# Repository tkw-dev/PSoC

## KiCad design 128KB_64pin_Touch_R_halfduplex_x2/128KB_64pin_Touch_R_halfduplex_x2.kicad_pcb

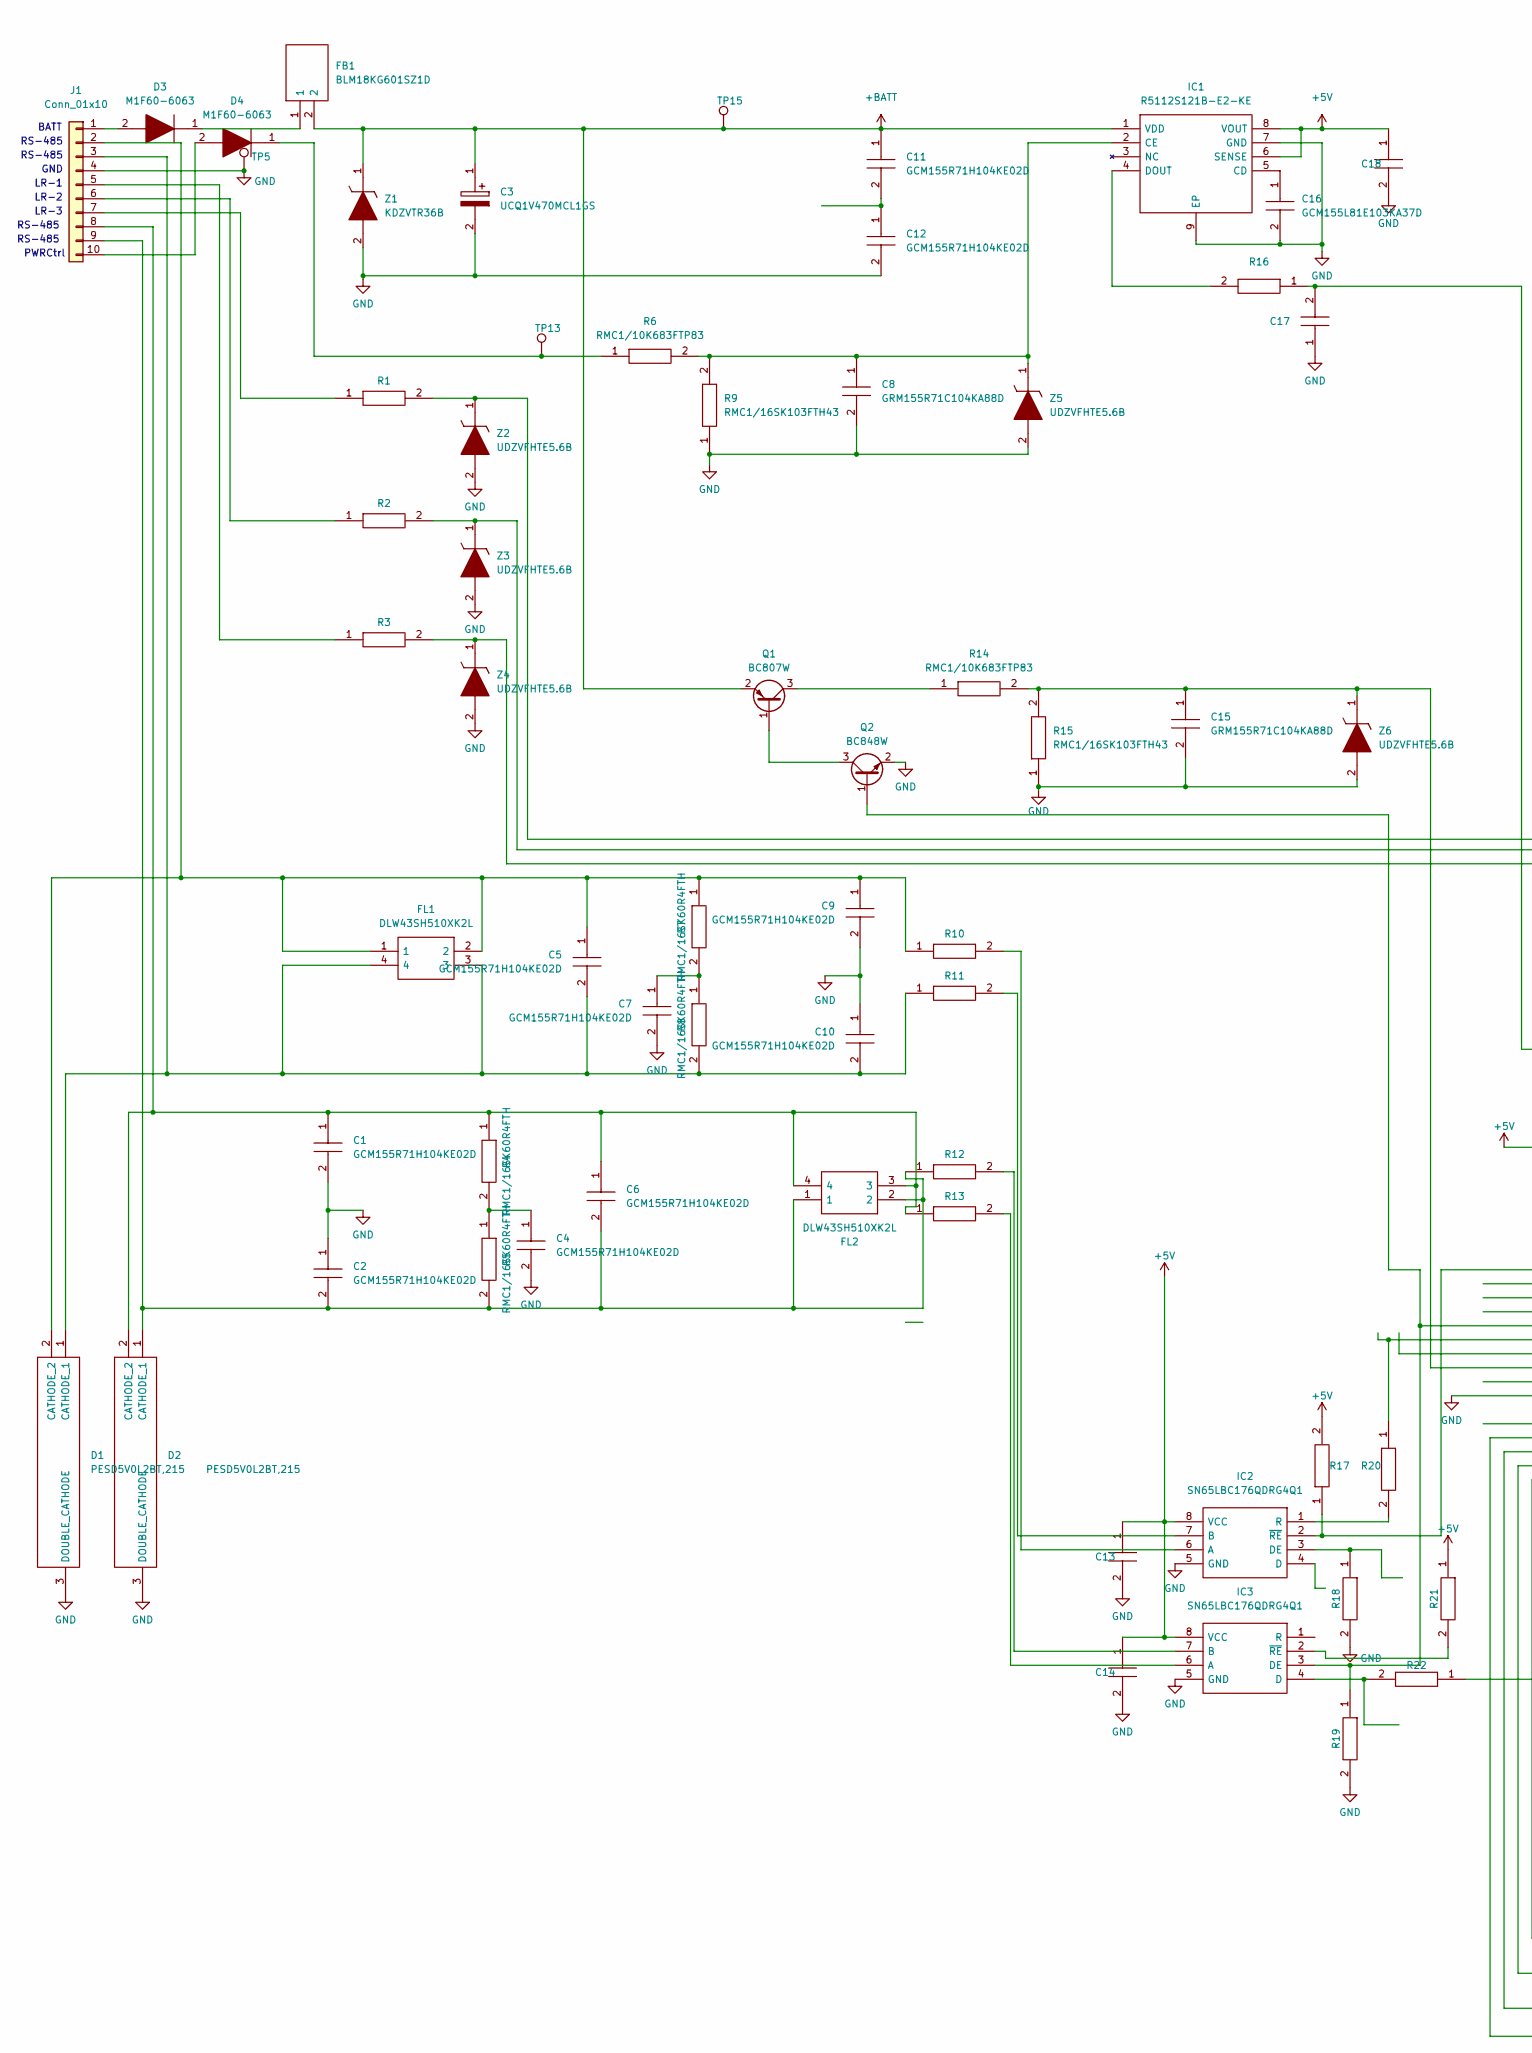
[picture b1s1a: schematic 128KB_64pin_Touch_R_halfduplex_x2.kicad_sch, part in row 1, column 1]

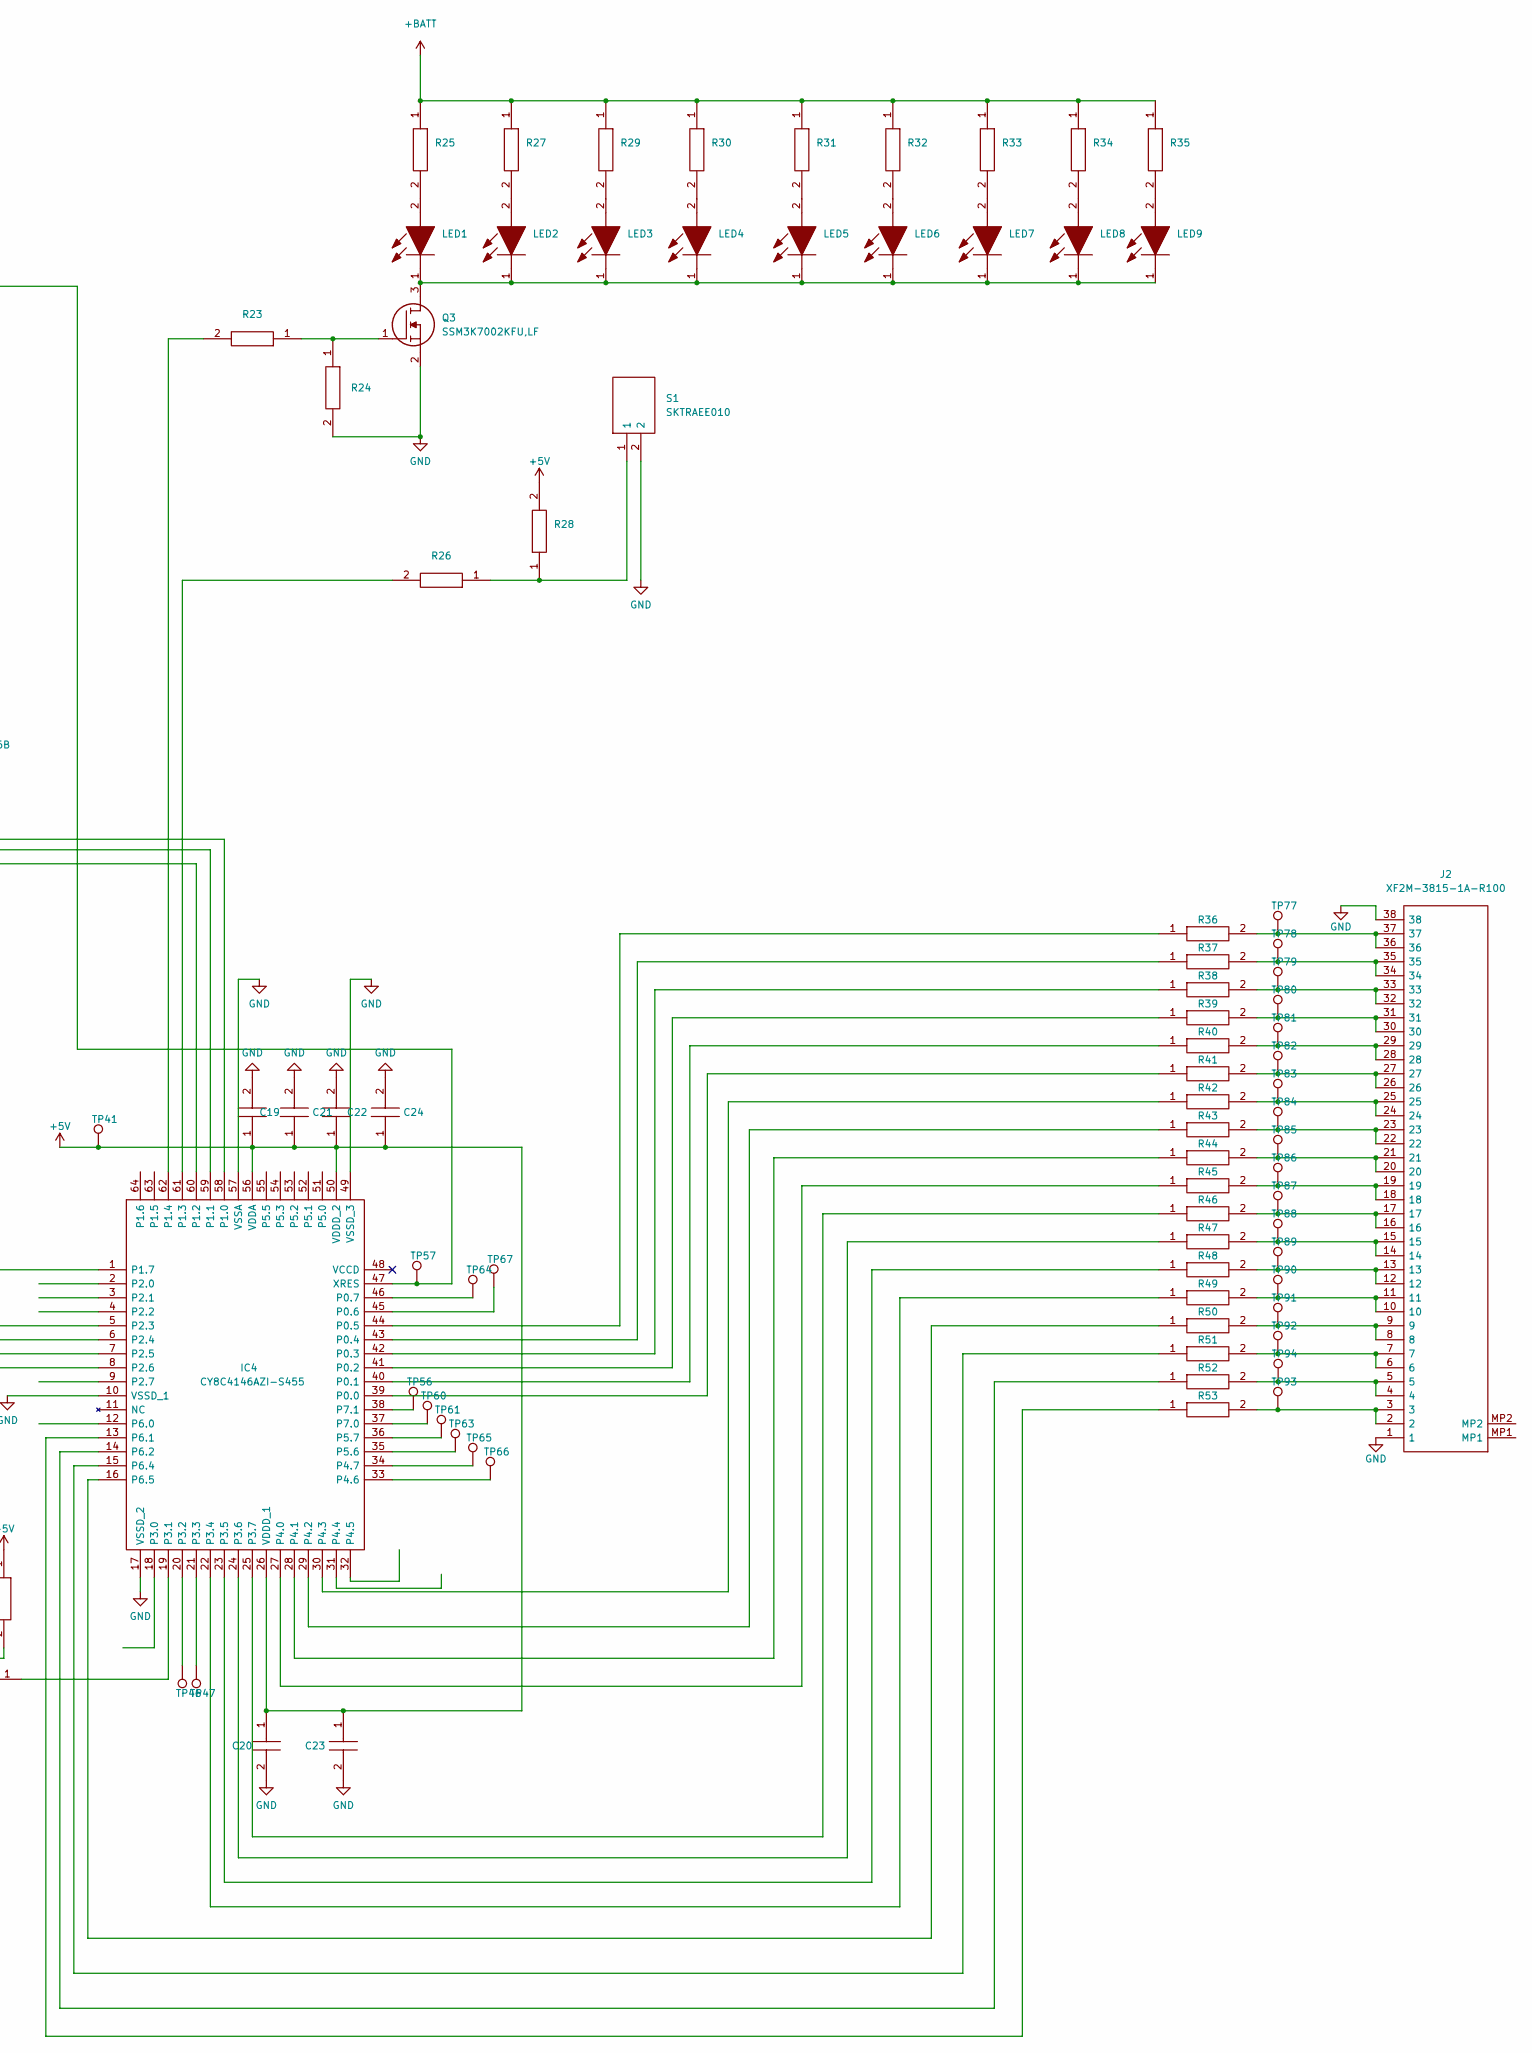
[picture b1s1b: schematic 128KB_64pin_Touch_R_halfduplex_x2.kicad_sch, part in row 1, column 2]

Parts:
C1, C2, C4, C5, C6, C7, C9, C10, C11, C12, C13, C14, C18, C19, C20, C22: GCM155R71H104KE02D; CAPC1005X55N; Mouser Part Number 81-GCM155R71H104KE2D
C3: UCQ1V470MCL1GS; CAPAE660X780N; Mouser Part Number 647-UCQ1V470MCL1GS
C8, C15: GRM155R71C104KA88D; CAPC1005X55N; Mouser Part Number N/A
C16: GCM155L81E103KA37D; CAPC1005X55N; Mouser Part Number 81-GCM155L81E103KA7D
C17: CL10B104JB8NNNC; CAPC1608X90N; Mouser Part Number 187-CL10B104JB8NNNC
C21, C23, C24: CGA3E2X5R1A105M080AA; CAPC1608X90N; Mouser Part Number 810-CGA3E2X5R1A105MA
D1, D2: PESD5V0L2BT,215; SOT95P230X110-3N; Manufacturer_Part_Number PESD5V0L2BT,215; Mouser Part Number 771-PESD5V0L2BT-T/R
D3, D4: M1F60-6063; SODFL3918X140N; Mouser Part Number 627-M1F60-6063
FB1: BLM18KG601SZ1D; BLM18EG121SH1D; Mouser Part Number 81-BLM18KG601SZ1D
FL1, FL2: DLW43SH510XK2L; DLW43SH110XK2K; Mouser Part Number 81-DLW43SH510XK2L
IC1: R5112S121B-E2-KE; SOIC127P620X160-9N; Manufacturer_Part_Number R5112S121B-E2-KE
IC2, IC3: SN65LBC176QDRG4Q1; SOIC127P600X175-8N; Mouser Part Number 595-N65LBC176QDRG4Q1
IC4: CY8C4146AZI-S455; QFP50P1200X1200X160-64N; Manufacturer_Part_Number CY8C4146AZI-S455; Mouser Part Number 727-CY8C4146AZI-S455
J1: Conn_01x10; JST_XH_B10B-XH-A_1x10_P2.50mm_Vertical
J2: XF2M-3815-1A-R100; XF2M38151AR100; Manufacturer_Part_Number XF2M-3815-1A-R100; Mouser Part Number 653-XF2M38151AR100
LED1, LED2, LED3, LED4, LED5, LED6, LED7, LED8, LED9: VLMR233T2V2-GS08; LEDM2214X140N; Mouser Part Number 78-VLMR233T2V2-GS08
Q1: BC807W; SOT-323_SC-70
Q2: BC848W; SOT-323_SC-70
Q3: SSM3K7002KFU,LF; SSM3K7002CFULF; Mouser Part Number 757-SSM3K7002KFULF
R1, R2, R3, R6, R14: RMC1/10K683FTP83; RESC2012X65N; Mouser Part Number 791-RMC1/10-103JTP
R4, R5, R7, R8: RMC1/16SK60R4FTH; RESC1608X55N; Manufacturer_Part_Number RMC16K270FTP
R9, R15, R23, R24, R26, R28: RMC1/16SK103FTH43; RESC1608X55N; Manufacturer_Part_Number RMC16K102FTP
R10, R11, R12, R13, R17, R18, R19, R20, R21, R22: RMC16K270FTP; RESC1608X55N; Manufacturer_Part_Number RMC16K270FTP
R16: RMC16K102FTP; RESC1608X55N; Manufacturer_Part_Number RMC16K102FTP
R25, R27, R29, R30, R31, R32, R33, R34, R35: ERJ-6ENF1502V; ERJ6ENF1000V; Mouser Part Number 667-ERJ-6ENF1502V
R36, R37, R38, R39, R40, R41, R42, R43, R44, R45, R46, R47, R48, R49, R50, R51, R52, R53: ERJ-2GEJ561X; RESC1005X40N; Mouser Part Number 667-ERJ-2GEJ561X
S1: SKTRAEE010; Mouser Part Number 688-SKTRAEE010
TP5, TP13, TP15, TP41, TP57, TP67: TestPoint; TestPoint_Pad_D2.5mm
TP46, TP47, TP56, TP60, TP61, TP63, TP64, TP65, TP66: TestPoint; TestPoint_Pad_D1.0mm
TP77, TP78, TP79, TP80, TP81, TP82, TP83, TP84, TP85, TP86, TP87, TP88, TP89, TP90, TP91, TP92, TP93, TP94: TestPoint; TestPoint_Pad_D0.5mm
Z1: KDZVTR36B; Mouser Part Number 755-KDZVTR36B
Z2, Z3, Z4, Z5, Z6: UDZVFHTE5.6B; SODFL2512X90N; Mouser Part Number 755-UDZVFHTE-175.6B

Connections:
+5V: C13.1, C14.1, C18.1, C19.1, C20.1, C21.1, C22.1, C23.1, C24.1, IC1.6 (SENSE), IC1.8 (VOUT), IC2.8 (VCC), IC3.8 (VCC), IC4.26 (VDDD_1), IC4.50 (VDDD_2), IC4.56 (VDDA), R17.2, R21.1, R28.2, TP41.1
+BATT: C3.1, C11.1, FB1.2, IC1.1 (VDD), Q1.2 (E), R25.1, R27.1, R29.1, R30.1, R31.1, R32.1, R33.1, R34.1, R35.1, TP15.1, Z1.1
GND: C1.2, C2.1, C3.2, C4.2, C7.2, C8.2, C9.2, C10.1, C12.2, C13.2, C14.2, C15.2, C16.2, C17.1, C18.2, C19.2, C20.2, C21.2, C22.2, C23.2, C24.2, D1.3 (DOUBLE_CATHODE), D2.3 (DOUBLE_CATHODE), IC1.7 (GND), IC1.9 (EP), IC2.5 (GND), IC3.5 (GND), IC4.10 (VSSD_1), IC4.17 (VSSD_2), IC4.49 (VSSD_3), IC4.57 (VSSA), J1.4, J2.1, J2.38, Q2.2 (E), Q3.2, R9.1, R15.1, R18.2, R19.2, R24.2, S1.2, TP5.1, Z1.2, Z2.2, Z3.2, Z4.2, Z5.2, Z6.2
unnamed: C1.1, C6.1, D2.2 (CATHODE_2), FL2.3, FL2.4, J1.8, R4.1, R13.1
unnamed: C4.1, R4.2, R5.1
unnamed: C5.1, C9.1, D1.2 (CATHODE_2), FL1.1, FL1.2, J1.2, R7.1, R10.1
unnamed: C7.1, R7.2, R8.1
unnamed: C5.2, C10.2, D1.1 (CATHODE_1), FL1.3, FL1.4, J1.3, R8.2, R11.1
unnamed: C11.2, C12.1
unnamed: C15.1, IC4.8 (P2.6), R14.2, R15.2, Z6.1
unnamed: C16.1, IC1.5 (CD)
unnamed: C17.2, IC4.47 (XRES), R16.1, TP57.1
unnamed: D3.1, FB1.1
unnamed: D3.2, J1.1
unnamed: D4.1, R6.1, TP13.1
unnamed: C2.2, C6.2, D2.1 (CATHODE_1), FL2.1, FL2.2, J1.9, R5.2, R12.1
unnamed: C8.1, IC1.2 (CE), R6.2, R9.2, Z5.1
unnamed: IC1.4 (DOUT), R16.2
unnamed: IC2.1 (R), R20.2
unnamed: IC2.2 (~RE), IC4.1 (P1.7), R17.1
unnamed: IC2.3 (DE), R18.1
unnamed: IC2.6 (A), R10.2
unnamed: IC2.7 (B), R11.2
unnamed: IC3.2 (~RE), R21.2
unnamed: IC3.3 (DE), IC4.5 (P2.3), Q2.1 (B), R19.1
unnamed: IC3.4 (D), R22.2
unnamed: IC3.6 (A), R13.2
unnamed: IC3.7 (B), R12.2
unnamed: IC4.6 (P2.4), R20.1
unnamed: IC4.13 (P6.1), R53.1
unnamed: IC4.14 (P6.2), R52.1
unnamed: IC4.15 (P6.4), R51.1
unnamed: IC4.16 (P6.5), R50.1
unnamed: IC4.19 (P3.1), R22.1
unnamed: IC4.20 (P3.2), TP46.1
unnamed: IC4.21 (P3.3), TP47.1
unnamed: IC4.22 (P3.4), R49.1
unnamed: IC4.23 (P3.5), R48.1
unnamed: IC4.24 (P3.6), R47.1
unnamed: IC4.25 (P3.7), R46.1
unnamed: IC4.27 (P4.0), R45.1
unnamed: IC4.28 (P4.1), R44.1
unnamed: IC4.29 (P4.2), R43.1
unnamed: IC4.30 (P4.3), R42.1
unnamed: IC4.33 (P4.6), TP66.1
unnamed: IC4.34 (P4.7), TP65.1
unnamed: IC4.35 (P5.6), TP63.1
unnamed: IC4.36 (P5.7), TP61.1
unnamed: IC4.37 (P7.0), TP60.1
unnamed: IC4.38 (P7.1), TP56.1
unnamed: IC4.39 (P0.0), R41.1
unnamed: IC4.40 (P0.1), R40.1
unnamed: IC4.41 (P0.2), R39.1
unnamed: IC4.42 (P0.3), R38.1
unnamed: IC4.43 (P0.4), R37.1
unnamed: IC4.44 (P0.5), R36.1
unnamed: IC4.45 (P0.6), TP67.1
unnamed: IC4.46 (P0.7), TP64.1
unnamed: IC4.58 (P1.0), R1.2, Z2.1
unnamed: IC4.59 (P1.1), R2.2, Z3.1
unnamed: IC4.60 (P1.2), R3.2, Z4.1
unnamed: IC4.61 (P1.3), R26.2
unnamed: IC4.62 (P1.4), R23.2
unnamed: J1.6, R2.1
unnamed: D4.2, J1.10
unnamed: J2.2, J2.3, R53.2, TP93.1
unnamed: J2.4, J2.5, R52.2, TP94.1
unnamed: J2.6, J2.7, R51.2, TP92.1
unnamed: J2.8, J2.9, R50.2, TP91.1
unnamed: J2.10, J2.11, R49.2, TP90.1
unnamed: J2.12, J2.13, R48.2, TP89.1
unnamed: J2.14, J2.15, R47.2, TP88.1
unnamed: J2.16, J2.17, R46.2, TP87.1
unnamed: J2.18, J2.19, R45.2, TP86.1
unnamed: J2.20, J2.21, R44.2, TP85.1
unnamed: J2.22, J2.23, R43.2, TP84.1
unnamed: J2.24, J2.25, R42.2, TP83.1
unnamed: J2.26, J2.27, R41.2, TP82.1
unnamed: J2.28, J2.29, R40.2, TP81.1
unnamed: J2.30, J2.31, R39.2, TP80.1
unnamed: J2.32, J2.33, R38.2, TP79.1
unnamed: J2.34, J2.35, R37.2, TP78.1
unnamed: J2.36, J2.37, R36.2, TP77.1
unnamed: LED1.2, R25.2
unnamed: LED2.2, R27.2
unnamed: LED3.2, R29.2
unnamed: LED4.2, R30.2
unnamed: LED5.2, R31.2
unnamed: LED7.2, R33.2
unnamed: LED8.2, R34.2
unnamed: Q1.1 (B), Q2.3 (C)
unnamed: Q1.3 (C), R14.1
unnamed: Q3.1, R23.1, R24.1
unnamed: LED1.1, LED2.1, LED3.1, LED4.1, LED5.1, LED6.1, LED7.1, LED8.1, LED9.1, Q3.3
unnamed: J1.7, R1.1
unnamed: J1.5, R3.1
unnamed: R26.1, R28.1, S1.1
unnamed: LED6.2, R32.2
unnamed: LED9.2, R35.2

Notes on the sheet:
RS-485
BATT
LR-1
LR-2
LR-3
GND
PWRCtrl

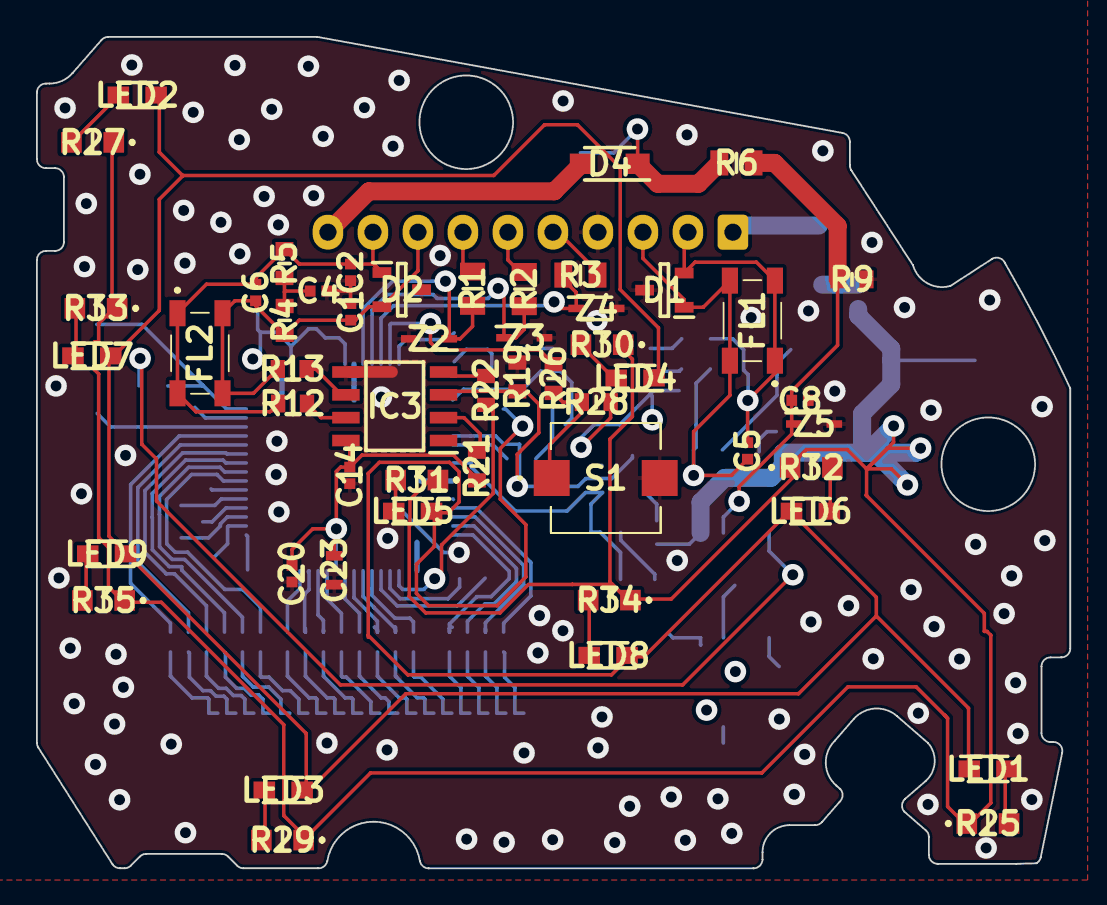
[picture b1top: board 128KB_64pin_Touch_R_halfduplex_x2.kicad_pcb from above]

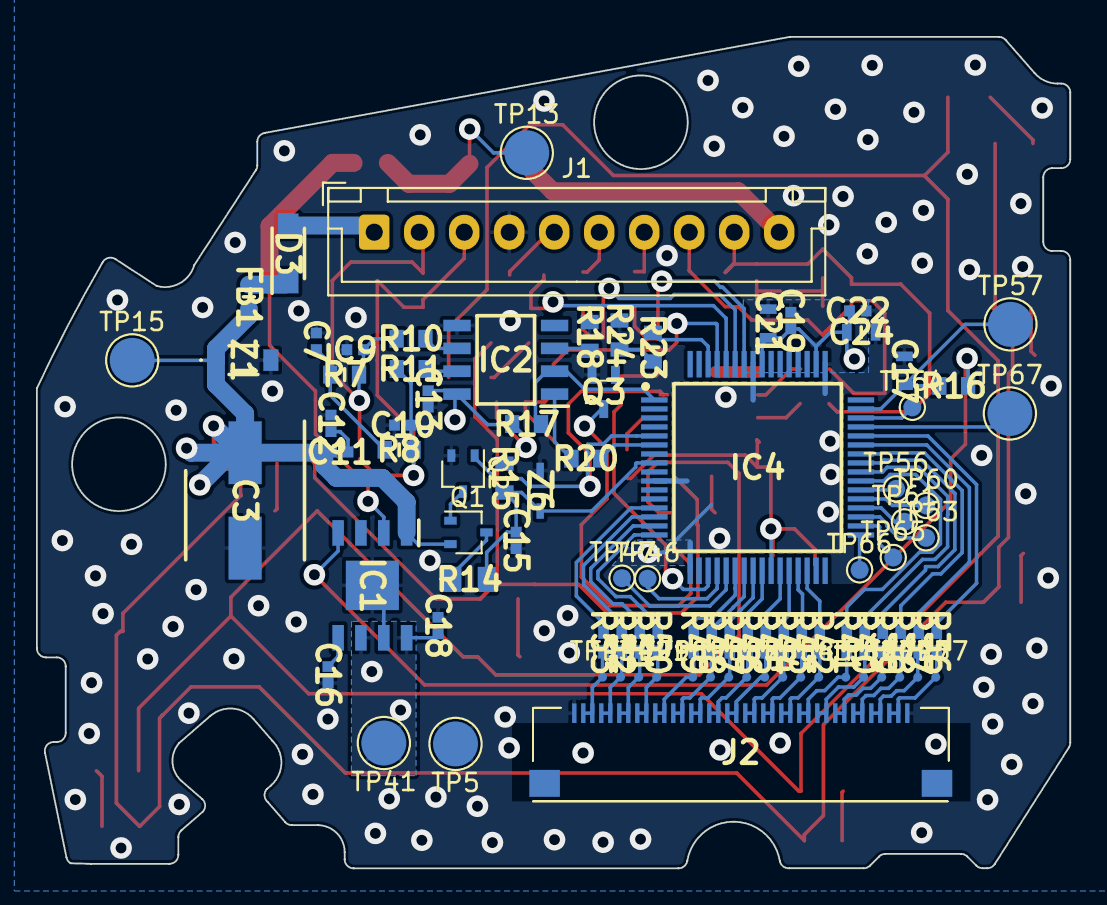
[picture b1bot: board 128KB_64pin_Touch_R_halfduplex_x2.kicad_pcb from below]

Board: 4 copper layers, 57.4 x 46.2 mm, 142 parts (90 on the bottom side), 99 nets.

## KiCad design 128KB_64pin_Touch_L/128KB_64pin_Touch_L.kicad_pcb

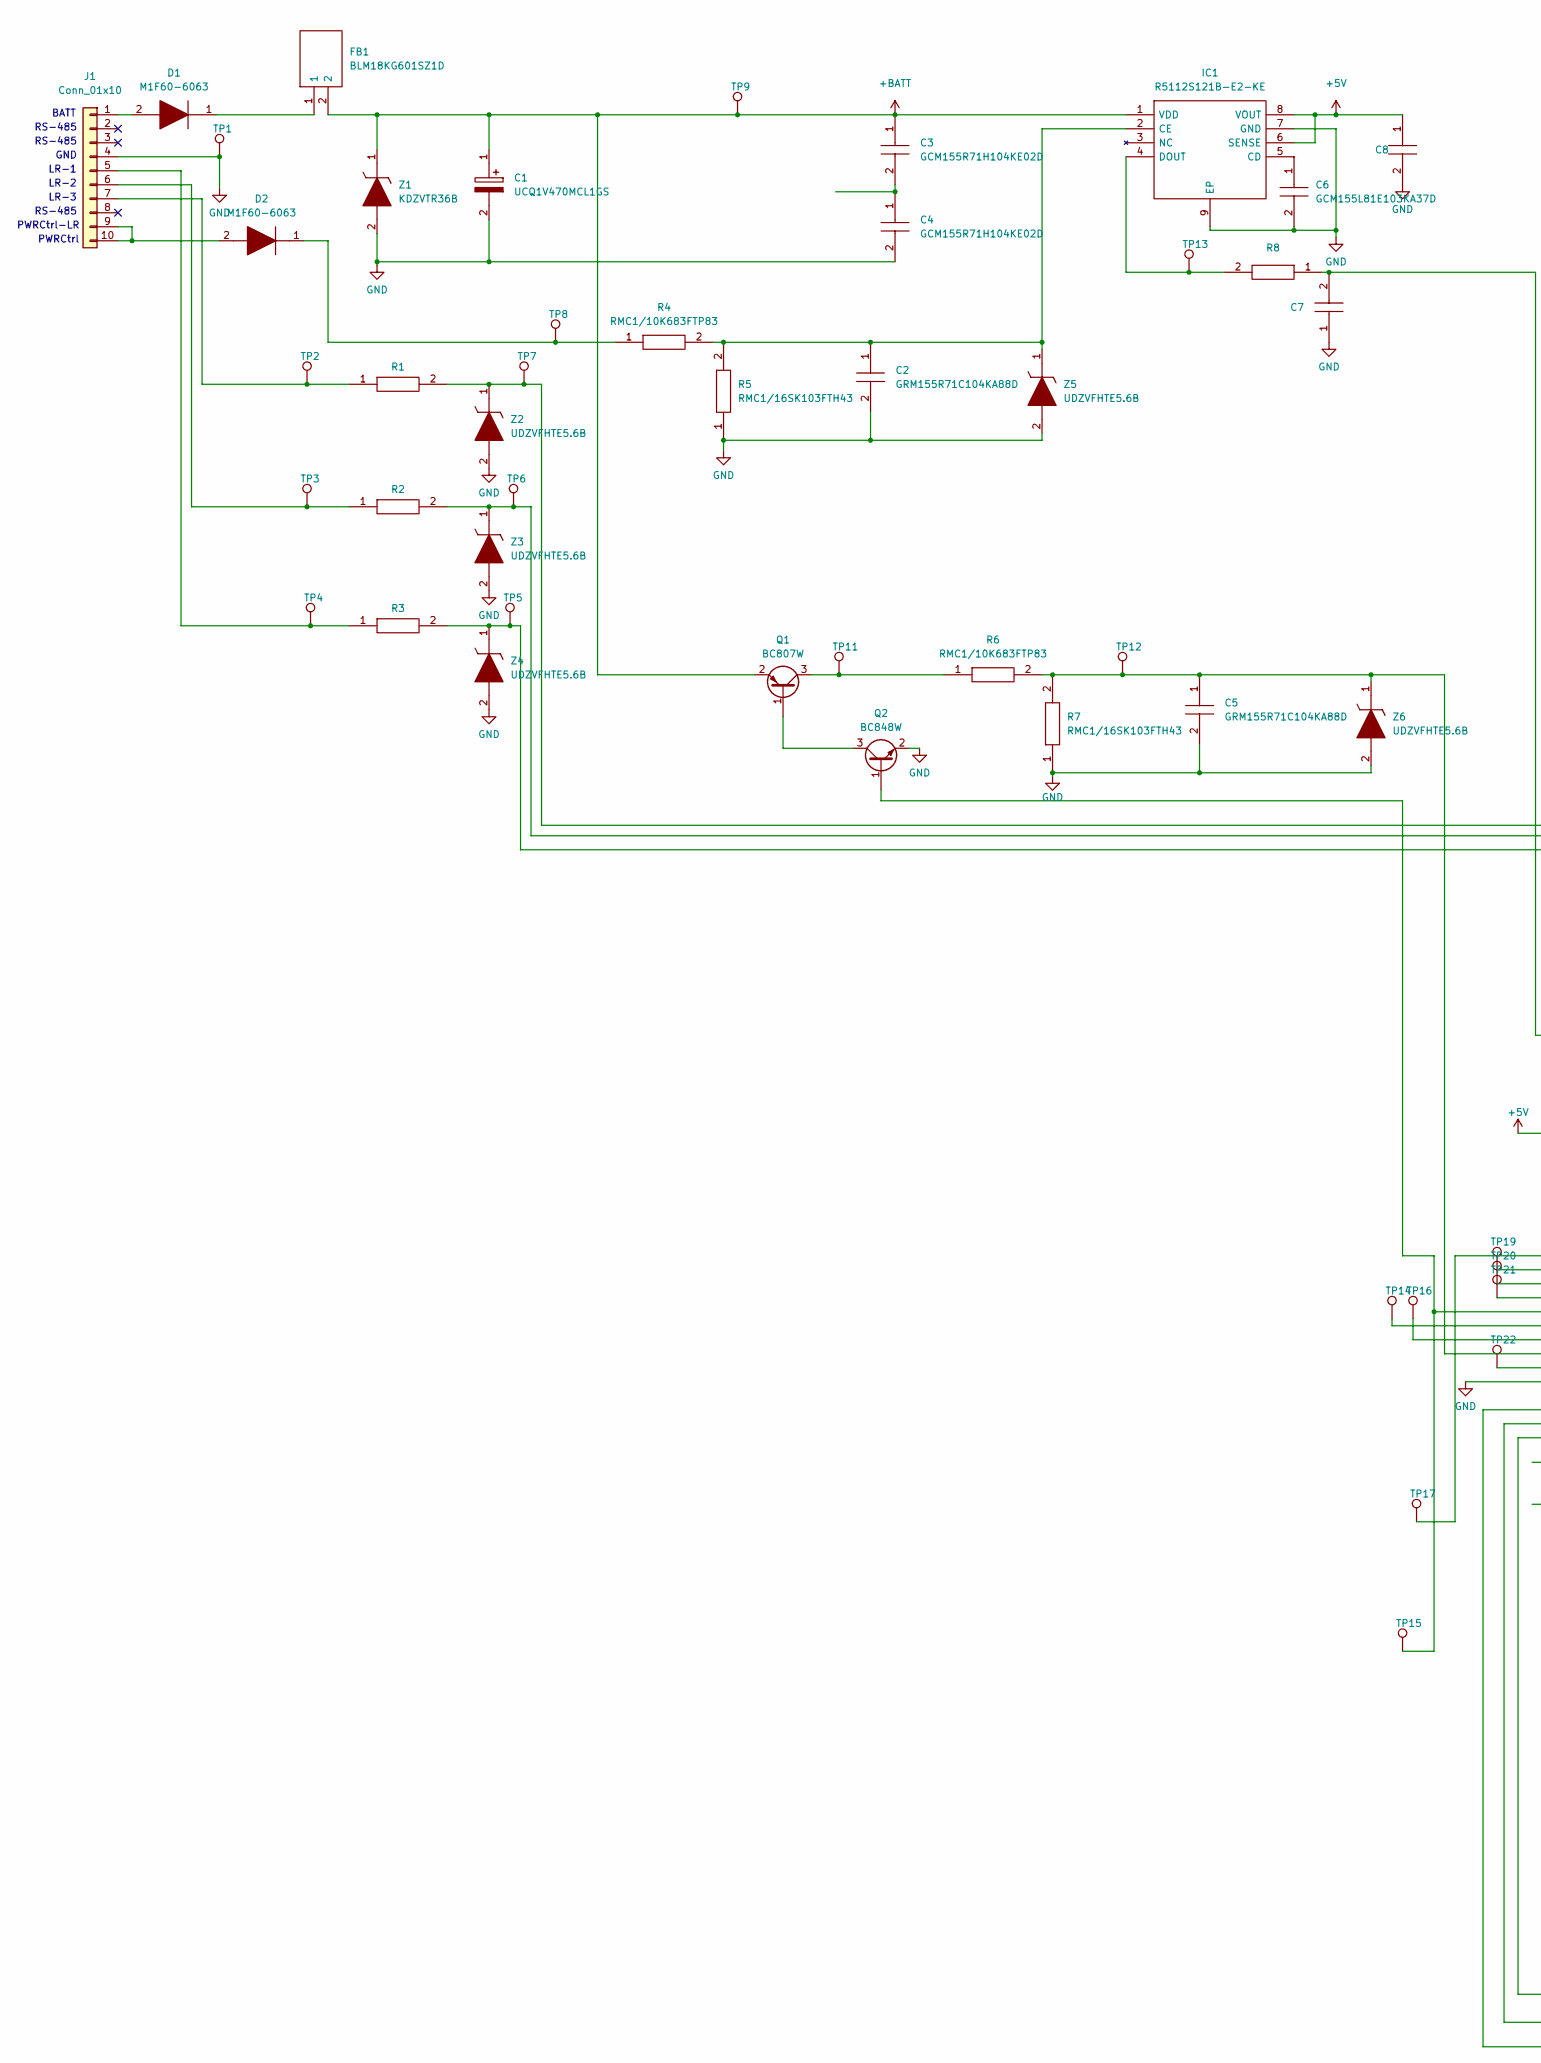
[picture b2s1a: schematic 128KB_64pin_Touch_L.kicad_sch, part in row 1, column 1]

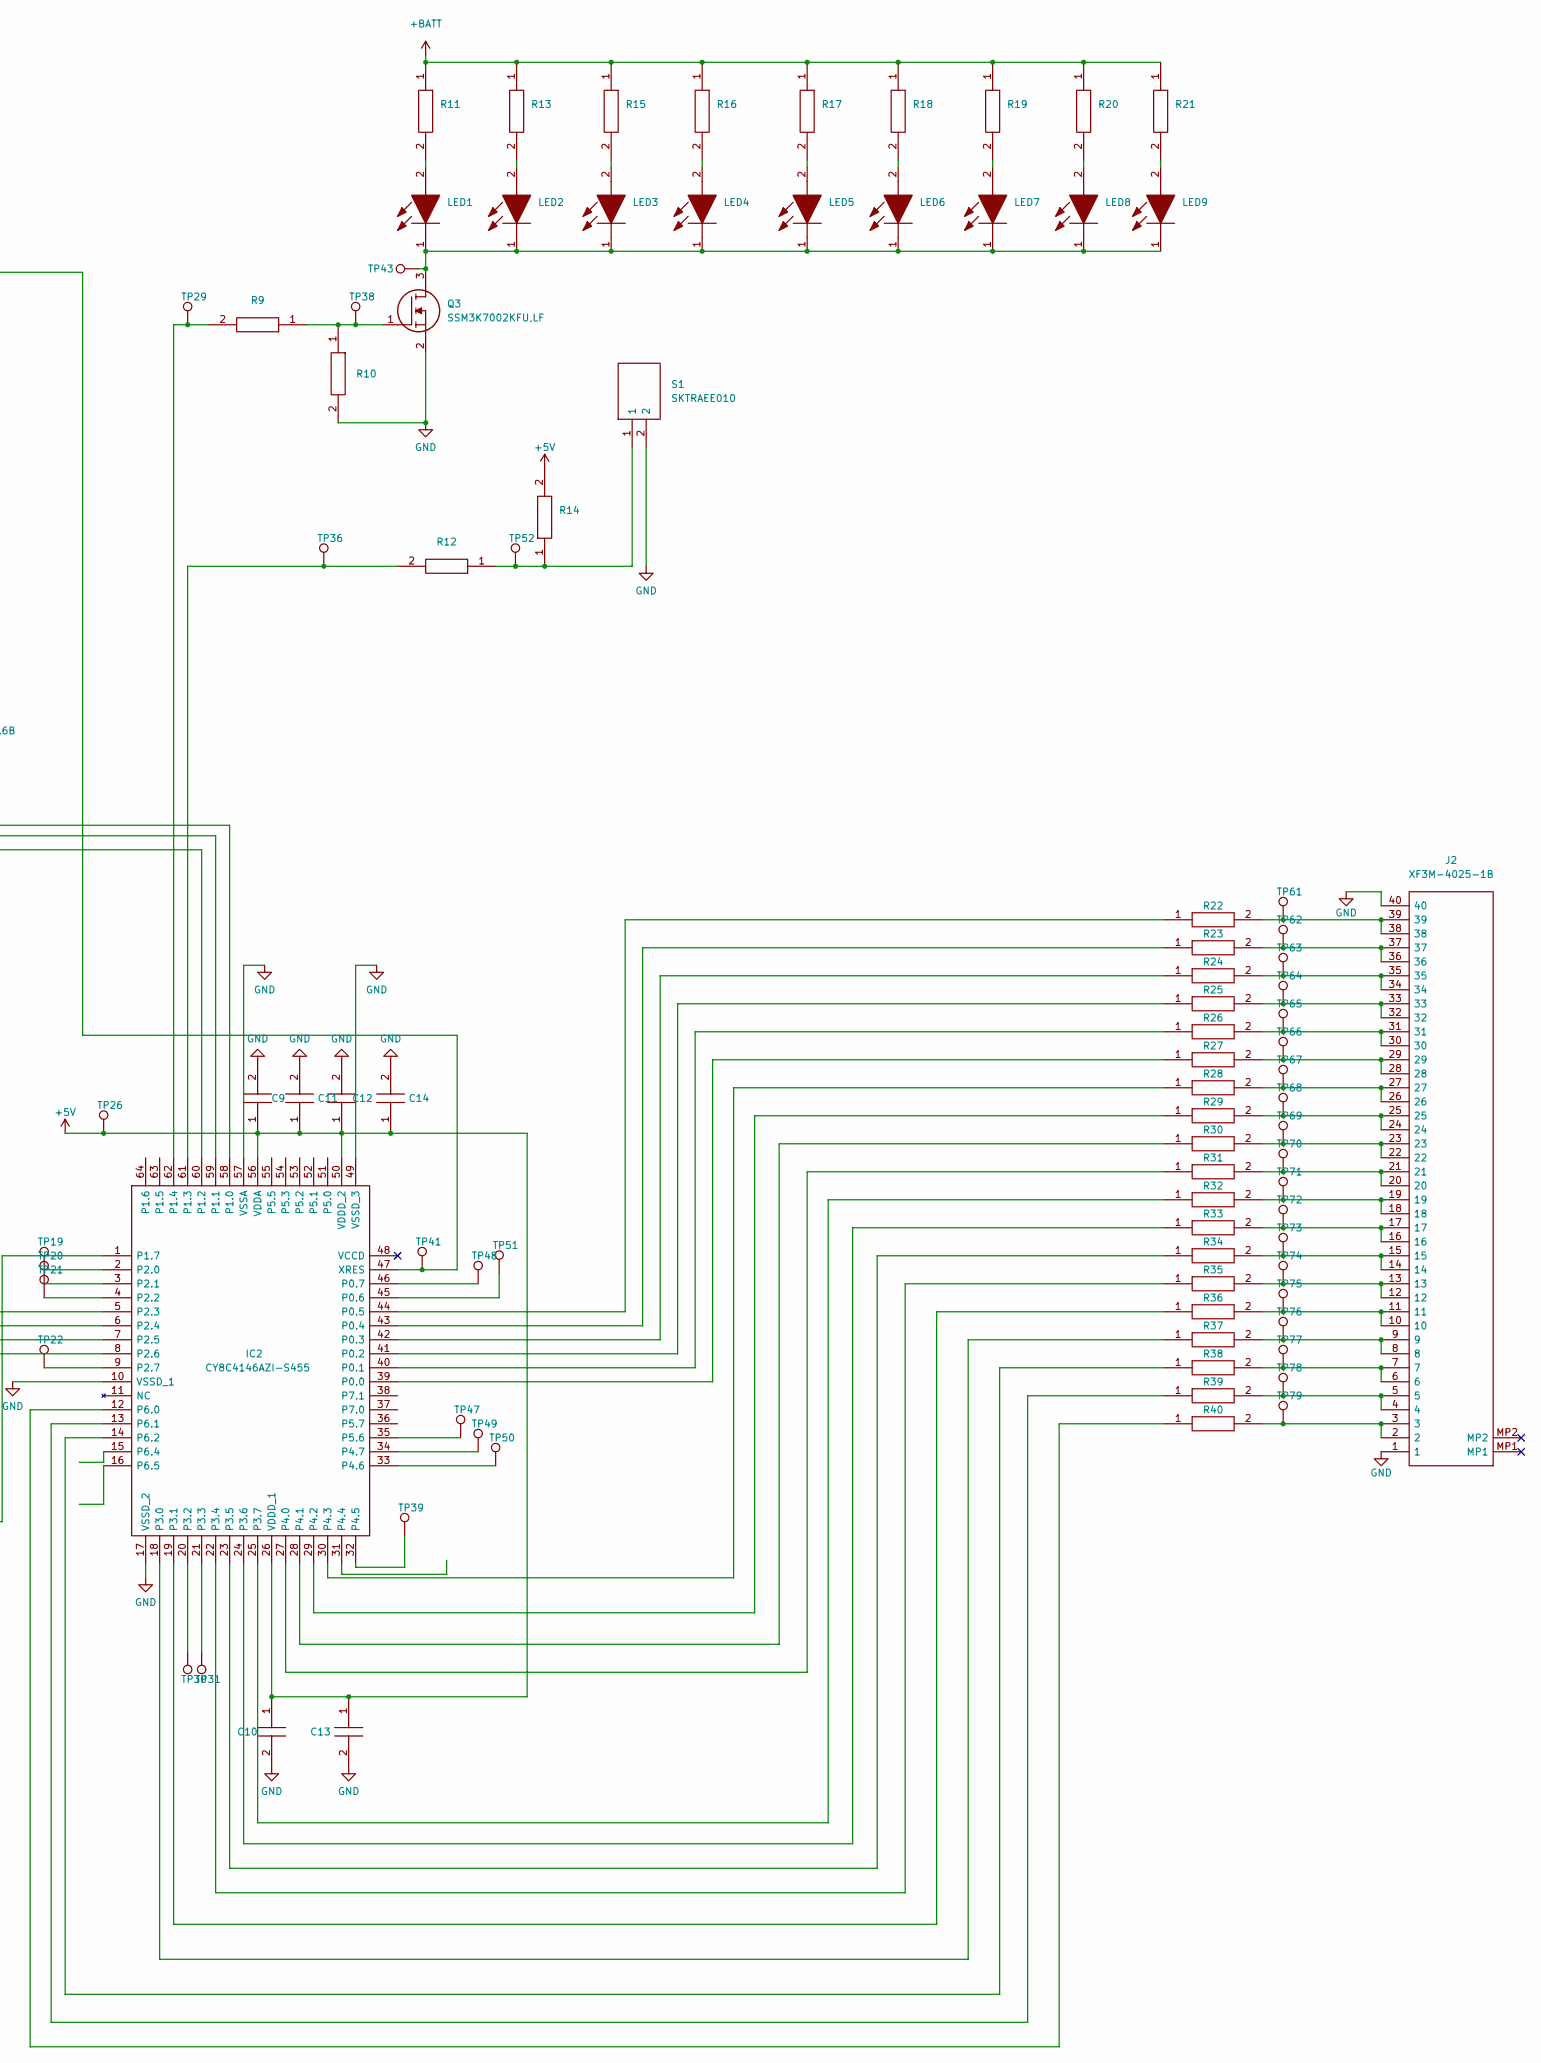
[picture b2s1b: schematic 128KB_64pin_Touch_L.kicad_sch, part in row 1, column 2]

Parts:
C1: UCQ1V470MCL1GS; CAPAE660X780N; Mouser Part Number 647-UCQ1V470MCL1GS
C2, C5: GRM155R71C104KA88D; CAPC1005X55N; Mouser Part Number N/A
C3, C4, C8, C9, C10, C12: GCM155R71H104KE02D; CAPC1005X55N; Mouser Part Number 81-GCM155R71H104KE2D
C6: GCM155L81E103KA37D; CAPC1005X55N; Mouser Part Number 81-GCM155L81E103KA7D
C7: CL10B104JB8NNNC; CAPC1608X90N; Mouser Part Number 187-CL10B104JB8NNNC
C11, C13, C14: CGA3E2X5R1A105M080AA; CAPC1608X90N; Mouser Part Number 810-CGA3E2X5R1A105MA
D1, D2: M1F60-6063; SODFL3918X140N; Mouser Part Number 627-M1F60-6063
FB1: BLM18KG601SZ1D; BLM18EG121SH1D; Mouser Part Number 81-BLM18KG601SZ1D
IC1: R5112S121B-E2-KE; SOIC127P620X160-9N; Manufacturer_Part_Number R5112S121B-E2-KE
IC2: CY8C4146AZI-S455; QFP50P1200X1200X160-64N; Manufacturer_Part_Number CY8C4146AZI-S455; Mouser Part Number 727-CY8C4146AZI-S455
J1: Conn_01x10; JST_XH_B10B-XH-A_1x10_P2.50mm_Vertical
J2: XF3M-4025-1B; XF3M40251B; Mouser Part Number 653-XF3M40251B
LED1, LED2, LED3, LED4, LED5, LED6, LED7, LED8, LED9: VLMR233T2V2-GS08; LEDM2214X140N; Mouser Part Number 78-VLMR233T2V2-GS08
Q1: BC807W; SOT-323_SC-70
Q2: BC848W; SOT-323_SC-70
Q3: SSM3K7002KFU,LF; SSM3K7002CFULF; Mouser Part Number 757-SSM3K7002KFULF
R1, R2, R3, R4, R6: RMC1/10K683FTP83; RESC2012X65N; Mouser Part Number 791-RMC1/10-103JTP
R5, R7, R9, R10, R12, R14: RMC1/16SK103FTH43; RESC1608X55N; Manufacturer_Part_Number RMC16K102FTP
R8: RMC16K102FTP; RESC1608X55N; Manufacturer_Part_Number RMC16K102FTP
R11, R13, R15, R16, R17, R18, R19, R20, R21: ERJ-6ENF1502V; ERJ6ENF1000V; Mouser Part Number 667-ERJ-6ENF1502V
R22, R23, R24, R25, R26, R27, R28, R29, R30, R31, R32, R33, R34, R35, R36, R37, R38, R39, R40: ERJ-2GEJ561X; RESC1005X40N; Mouser Part Number 667-ERJ-2GEJ561X
S1: SKTRAEE010; Mouser Part Number 688-SKTRAEE010
TP1, TP8, TP9, TP26, TP41, TP51: TestPoint; TestPoint_Pad_D2.5mm
TP2, TP3, TP4, TP5, TP6, TP7, TP11, TP12, TP13, TP14, TP15, TP16, TP17, TP19, TP20, TP21, TP22, TP29, TP30, TP31, TP36, TP38, TP39, TP43, TP47, TP48, TP49, TP50, TP52: TestPoint; TestPoint_Pad_D1.0mm
TP61, TP62, TP63, TP64, TP65, TP66, TP67, TP68, TP69, TP70, TP71, TP72, TP73, TP74, TP75, TP76, TP77, TP78, TP79: TestPoint; TestPoint_Pad_D0.5mm
Z1: KDZVTR36B; Mouser Part Number 755-KDZVTR36B
Z2, Z3, Z4, Z5, Z6: UDZVFHTE5.6B; SODFL2512X90N; Mouser Part Number 755-UDZVFHTE-175.6B

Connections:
+5V: C8.1, C9.1, C10.1, C11.1, C12.1, C13.1, C14.1, IC1.6 (SENSE), IC1.8 (VOUT), IC2.26 (VDDD_1), IC2.50 (VDDD_2), IC2.56 (VDDA), R14.2, TP26.1
+BATT: C1.1, C3.1, FB1.2, IC1.1 (VDD), Q1.2 (E), R11.1, R13.1, R15.1, R16.1, R17.1, R18.1, R19.1, R20.1, R21.1, TP9.1, Z1.1
GND: C1.2, C2.2, C4.2, C5.2, C6.2, C7.1, C8.2, C9.2, C10.2, C11.2, C12.2, C13.2, C14.2, IC1.7 (GND), IC1.9 (EP), IC2.10 (VSSD_1), IC2.17 (VSSD_2), IC2.49 (VSSD_3), IC2.57 (VSSA), J1.4, J2.1, J2.40, Q2.2 (E), Q3.2, R5.1, R7.1, R10.2, S1.2, TP1.1, Z1.2, Z2.2, Z3.2, Z4.2, Z5.2, Z6.2
unnamed: C2.1, IC1.2 (CE), R4.2, R5.2, Z5.1
unnamed: C3.2, C4.1
unnamed: C5.1, IC2.8 (P2.6), R6.2, R7.2, TP12.1, Z6.1
unnamed: C6.1, IC1.5 (CD)
unnamed: C7.2, IC2.47 (XRES), R8.1, TP41.1
unnamed: D1.1, FB1.1
unnamed: D1.2, J1.1
unnamed: D2.1, R4.1, TP8.1
unnamed: D2.2, J1.9, J1.10
unnamed: IC1.4 (DOUT), R8.2, TP13.1
unnamed: IC2.1 (P1.7), TP17.1
unnamed: IC2.2 (P2.0), TP19.1
unnamed: IC2.3 (P2.1), TP20.1
unnamed: IC2.4 (P2.2), TP21.1
unnamed: IC2.5 (P2.3), Q2.1 (B), TP15.1
unnamed: IC2.6 (P2.4), TP14.1
unnamed: IC2.7 (P2.5), TP16.1
unnamed: IC2.9 (P2.7), TP22.1
unnamed: IC2.12 (P6.0), R40.1
unnamed: IC2.13 (P6.1), R39.1
unnamed: IC2.14 (P6.2), R38.1
unnamed: IC2.18 (P3.0), R37.1
unnamed: IC2.19 (P3.1), R36.1
unnamed: IC2.20 (P3.2), TP30.1
unnamed: IC2.21 (P3.3), TP31.1
unnamed: IC2.22 (P3.4), R35.1
unnamed: IC2.23 (P3.5), R34.1
unnamed: IC2.24 (P3.6), R33.1
unnamed: IC2.25 (P3.7), R32.1
unnamed: IC2.27 (P4.0), R31.1
unnamed: IC2.28 (P4.1), R30.1
unnamed: IC2.29 (P4.2), R29.1
unnamed: IC2.30 (P4.3), R28.1
unnamed: IC2.32 (P4.5), TP39.1
unnamed: IC2.33 (P4.6), TP50.1
unnamed: IC2.34 (P4.7), TP49.1
unnamed: IC2.35 (P5.6), TP47.1
unnamed: IC2.39 (P0.0), R27.1
unnamed: IC2.40 (P0.1), R26.1
unnamed: IC2.41 (P0.2), R25.1
unnamed: IC2.42 (P0.3), R24.1
unnamed: IC2.43 (P0.4), R23.1
unnamed: IC2.44 (P0.5), R22.1
unnamed: IC2.45 (P0.6), TP51.1
unnamed: IC2.46 (P0.7), TP48.1
unnamed: IC2.58 (P1.0), R1.2, TP7.1, Z2.1
unnamed: IC2.59 (P1.1), R2.2, TP6.1, Z3.1
unnamed: IC2.60 (P1.2), R3.2, TP5.1, Z4.1
unnamed: IC2.61 (P1.3), R12.2, TP36.1
unnamed: IC2.62 (P1.4), R9.2, TP29.1
unnamed: J1.5, R3.1, TP4.1
unnamed: J1.6, R2.1, TP3.1
unnamed: J1.7, R1.1, TP2.1
unnamed: J2.2, J2.3, R40.2, TP79.1
unnamed: J2.4, J2.5, R39.2, TP78.1
unnamed: J2.6, J2.7, R38.2, TP77.1
unnamed: J2.8, J2.9, R37.2, TP76.1
unnamed: J2.10, J2.11, R36.2, TP75.1
unnamed: J2.12, J2.13, R35.2, TP74.1
unnamed: J2.14, J2.15, R34.2, TP73.1
unnamed: J2.16, J2.17, R33.2, TP72.1
unnamed: J2.18, J2.19, R32.2, TP71.1
unnamed: J2.20, J2.21, R31.2, TP70.1
unnamed: J2.22, J2.23, R30.2, TP69.1
unnamed: J2.24, J2.25, R29.2, TP68.1
unnamed: J2.26, J2.27, R28.2, TP67.1
unnamed: J2.28, J2.29, R27.2, TP66.1
unnamed: J2.30, J2.31, R26.2, TP65.1
unnamed: J2.32, J2.33, R25.2, TP64.1
unnamed: J2.34, J2.35, R24.2, TP63.1
unnamed: J2.36, J2.37, R23.2, TP62.1
unnamed: J2.38, J2.39, R22.2, TP61.1
unnamed: LED1.2, R11.2
unnamed: LED2.2, R13.2
unnamed: LED8.2, R20.2
unnamed: LED9.2, R21.2
unnamed: Q1.1 (B), Q2.3 (C)
unnamed: Q1.3 (C), R6.1, TP11.1
unnamed: Q3.1, R9.1, R10.1, TP38.1
unnamed: LED1.1, LED2.1, LED3.1, LED4.1, LED5.1, LED6.1, LED7.1, LED8.1, LED9.1, Q3.3, TP43.1
unnamed: R12.1, R14.1, S1.1, TP52.1
unnamed: LED3.2, R15.2
unnamed: LED4.2, R16.2
unnamed: LED5.2, R17.2
unnamed: LED6.2, R18.2
unnamed: LED7.2, R19.2

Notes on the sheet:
PWRCtrl-LR
RS-485
BATT
LR-1
LR-2
LR-3
GND
PWRCtrl
